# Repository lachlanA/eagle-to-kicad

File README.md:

### **Converting from Eagle to KiCad.**
*    [Quick Introduction Video (DEAD LINK, MOVING to NEW SERVER)](http://cosmosc.com/video/testtital.mp4)  
     *Recommended video player [Firefox 87.0+](https://www.mozilla.org/en-US/firefox/desktop/) with [VLC video player plugin](http://www.videolan.org/vlc/)*  

* The following 5 **ulp** (eagle *user script file*) and one **ulp** include file, work together or stand alone to convert **Eagle** *sch/pcb* version 6.xx*(7.xx-8.xx maybe?)* file(s) and any version of Eagle lib(*lbr*) to **KiCad** *sch/pcb* and *lib/mod* files.  

* The Programs will do
    * Eagle multi sheet schematic to KiCad multi sheets.  
	* Global and local net labels for multi sheets. *(This is a real nasty bit of hacking!)*
	* Multi part gates.  
	* Build KiCad PCB modules and sch libs from Eagle sch.  
	* Make project director to store all the converted files.  
	* And basic error checking.  
	* Eagle 6.xx(7.xx-8.xx?) PCB files can be directly import to KiCad.  
	* Eagle *LBR*s (any version of Eagle libs or size ) can be converted to KiCad lib/mod using eagle-lbr2kicad-1.0.ulp see [Eagle Lib conversion]( https://github.com/lachlanA/eagle-to-kicad-libs) for more details.  
	* Converts VIA to Pads, which helps with KiCad's flood fill, when VIAs have no connections.  
	* Documents fills over SMD pads on Eagle Layer 155,156  
	* Documents on layer's 150,152,153,154 of (Eagle) the unconnected VIAs and tracks.  
	* The **[examples](https://github.com/lachlanA/eagle-to-kicad/tree/master/examples)** directory contains a number of converted schematics/boards.  

* By using the following **ulp**s  a consistent link from the schematic to PCB is maintained so forward and backward net-list annotations work under KiCad!  

* **WARNINGS, AND NASTY SURPRISES, PLEASE READ!!!**
* **Only works correctly for version 4.7, or 5.1.(X?) of KiCad, it may not on other version.**
* **In KiCad Eagle PCB import of vias and tracks don't retain their NET information if they are not connected to a pad with a track, whereas they do in Eagle, (KiCad assigns a null net-name on Eagle PCB import in KiCad's Pcbnew).***  
***The result will be KiCad flood fill will not connect to them!!! There is an option to convert and document on layers 150,152,153,154 of (Eagle) the unconnected VIAs and tracks which will make finding and fixing the problem much easier.***
* ***Schematics wire's/nets can terminate in a bus or onto another wire/net/pad and not be connected in Eagle!!
Whereas in KiCad schematic wires to wires and wires to pads which terminates at the same location will be connected!!***  
* ***Eagle oval pad shapes are not supported in KiCad, you will only end up with a round pad!!***  
* ***Eagle PCB design rules are not imported by KiCads Pcbnew.***  

### Installing.
* Download the zip file, and unzip using your favorite zip program to your target directory *OR* if your prefer git:

			git clone https://github.com/lachlanA/eagle-to-kicad.git  

* **WARNING:**  The ULPs file-name will conflict with Eagles ULPs file-names so  
  **DO NOT install them in Eagle's ULP directory**  

* There are 5 **ULPs** and one **ULP** include file have been hack together.  
***run-me-first-from-eagle-sch.ulp*** .....   stage 1: Start here,  script missing number(s) to parts prefixes.  
***fix_via_hack.ulp*** ..............................   stage 2: Converts unconnected VIAs to pads.  
***eagle6xx-sch-to-kicad-sch.ulp*** ....    stage 3: Build sch and project files, etc  
***exp-lbrs.ulp*** .......................................   stage 4: Extract libs from eagle schematic/PCB  
***eagle-lbr2kicad-1.0.ulp***....................  stage 5: Converts Eagle lbr to KiCad lib/mod  
***eagle_to_kicad_include.inc*** ..........  Include file used by the other 4 ULP\s  

### HOW TO RUN THE ULPs 
 
 **WARNING Always backup your Eagle sch/PCB files before running this program!**  
 
1. Start your Eagle program *(Make sure your using  version 6.xx of Eagle)*

2. Open the eagle sch/PCB  file you wish to convert. Make sure the eagle sch and PCB files are both, Correct and pass all ERC/DRC checks in Eagle.  

3. Next Open the top left hand  **File menu** and select  **Run ULP**  

4. A file requester window will open. Use this to find the location of the ***run-me-first-from-eagle-sch.ulp*** ULP you download from this website. We use this script to make sure all part prefixes are ending in a number  IE:   R0,  X1   etc. as KiCad will ask to renumber any prefix which does not end in a number. *(It may do this any way, but don't worry it won't change any prefixes which have already been numbered unless you tell it too!)*  Keeping prefixes consistent from schematic to PCB will allow net-list forward and back annotation to work in KiCad. Select **OK** *(this will run the script)*.  When this completes all references without a number should have a number appended to them. Note: This number will start from the largest reference number on the sch/PCB.

5. Next stage will run automatically, ***fix_via_hack.ulp*** This will check for free unconnected VIAs and convert them to pads,  this is very much a hack, as it changes the Eagle sch/PCB files.  The changed files are saved in ***targetdir/modified_eagle_files/*** There are 2 option's Document the VIAs/pads buy putting a ***>*** and net lable name on the VIA/pad on **layer 51** for Eagle, and **Dwgs.User** for KiCad. Second option is to Not to convert the VIAs to pads.  
The ulp hack adds pad's to the sch file, at **X,Y 0,0** this may conflict with any net/part at this location, so please move the sch/PCB contents so there are no parts/nets at this location before running the script.
You may getting warnings from Eagle about connecting net??? to a power plan net, just click OK, as this is normal for this script.

6. Next stage will run automatically. Set the option/location of the download ULP. And also Make sure you make/select a ***clean target directory*** where all the KiCad files will be put. Select OK, And with luck you should have sch part done. The previous ULP will link automatically to ***exp-lbrs.ulp*** for the  next step: If you have selected extract the KiCad lib's from Eagle sch/PCB *(The default).* This ULP will build Eagle lbr file, *Note: this can be a very slow process,  and will leave the Eagle PCB editor window open when complete*. Just ignore this for the moment. If this complete OK, the previous ULP will link to ***eagle-lbr2kicad-1.0.ulp*** which will convert the Eagle lbr file to a KiCad lib/mod files.  The ***eagle-lbr2kicad-1.0.ulp*** window will open with quite a few options. Just select OK for the moment.  And if *Murphy's Law is sound asleep* we should have the target directory with all the converted files, including KiCad project files. But with one exception, it will be missing KiCad PCB file.

7. For this, we need to Open KiCad's **pcbnew** program directly, at the command prompt ("c:\Program Files\KiCad\bin\pcbnew.exe"). *If you make the mistake of not opening **pcbnew** directly, and instead chose to run it from KiCad's **pcbnew**  menu. You will have no option for importing the Eagle 6 PCB file!*  In Pcbnew click on **File->Import Non-KiCad Board File...**, a window will pop-up. Select the PCB eagle file linked to the eagle sch file we used at the beginning. On the lower right side you will have a drop down menu box option, select **Eagle ver. 6.x XML PCB files (\*.b**, and press OK. After importing the Eagle PCB file, (without errors I hope). Do a **SAVE AS** to **PROJECTNAME.kicad_pcb** to the new target directory *(where you saved the output from to preceding ULP's to).* **PROJECTNAME** being the name you give to your project early on. As a helper a dummy kicad_pcb file with the correct name has been created in the target directory which you can use to do a Save-As to.

8. Next step is to check the KiCad **sch** and KiCad **PCB** are consistent for parts and nets. Start **KiCad**, and open the project in the newly created target directory. Open the sch file. And if it was converted from the single sch file, you should have the **sch** file in the display. Or multi sheet **sch** file you will have a number of small boxes spread across the page. Each one of those boxes being a converted Eagle sub-sheet. Click on the first one and check for errors. All being good, click on Generate Net-list, and click OK. It may ask to Annotate the **schematic**. If so do the Annotation step. And then come back and click on Generate net-list. And Generate it.

9. Next click on **CvPcb**, this assigns the PCB footprints with the sch parts. Most likely you will get the following warning: *Some of the assigned footprints are legacy entries (are missing lib nicknames). Would you like CvPcb to attempt to convert them to the new required FPID format? (If you answer no, then these assignments will be cleared out and you will have to re-assign these footprints yourself.)* Just click the yes button. And a window will open up listing all the parts and footprints which it has assigned. Under FILE menu click Save. And then File Close.

10. Next Clink on **PcbNew** button on the top menu, and the PCB should open up. Now click on the **NetList** and a window should open up, from there click on Read Current Net-list. All going well you should not have any extra parts added, and only a few warning's about changing net list names.  And you should be done. Please check over the converted **sch/PCB** as there are many things which can go wrong! While I have tried to catch as many conversion problem, I expect there many still waiting to be found. ***So check and triple check the results!!!***

**NOTES:**   For more info on KiCad https://www.kicad.org/display/KICAD/Installing+KiCad  
As KiCad is the process of major upgrade, and enhancement. Please be nice when asking questions of the Development team. I think you will love the new Push and shove router. This feature alone makes it worth while moving from Eagle to KiCad. I hope these ULPs make the job a lot easier.

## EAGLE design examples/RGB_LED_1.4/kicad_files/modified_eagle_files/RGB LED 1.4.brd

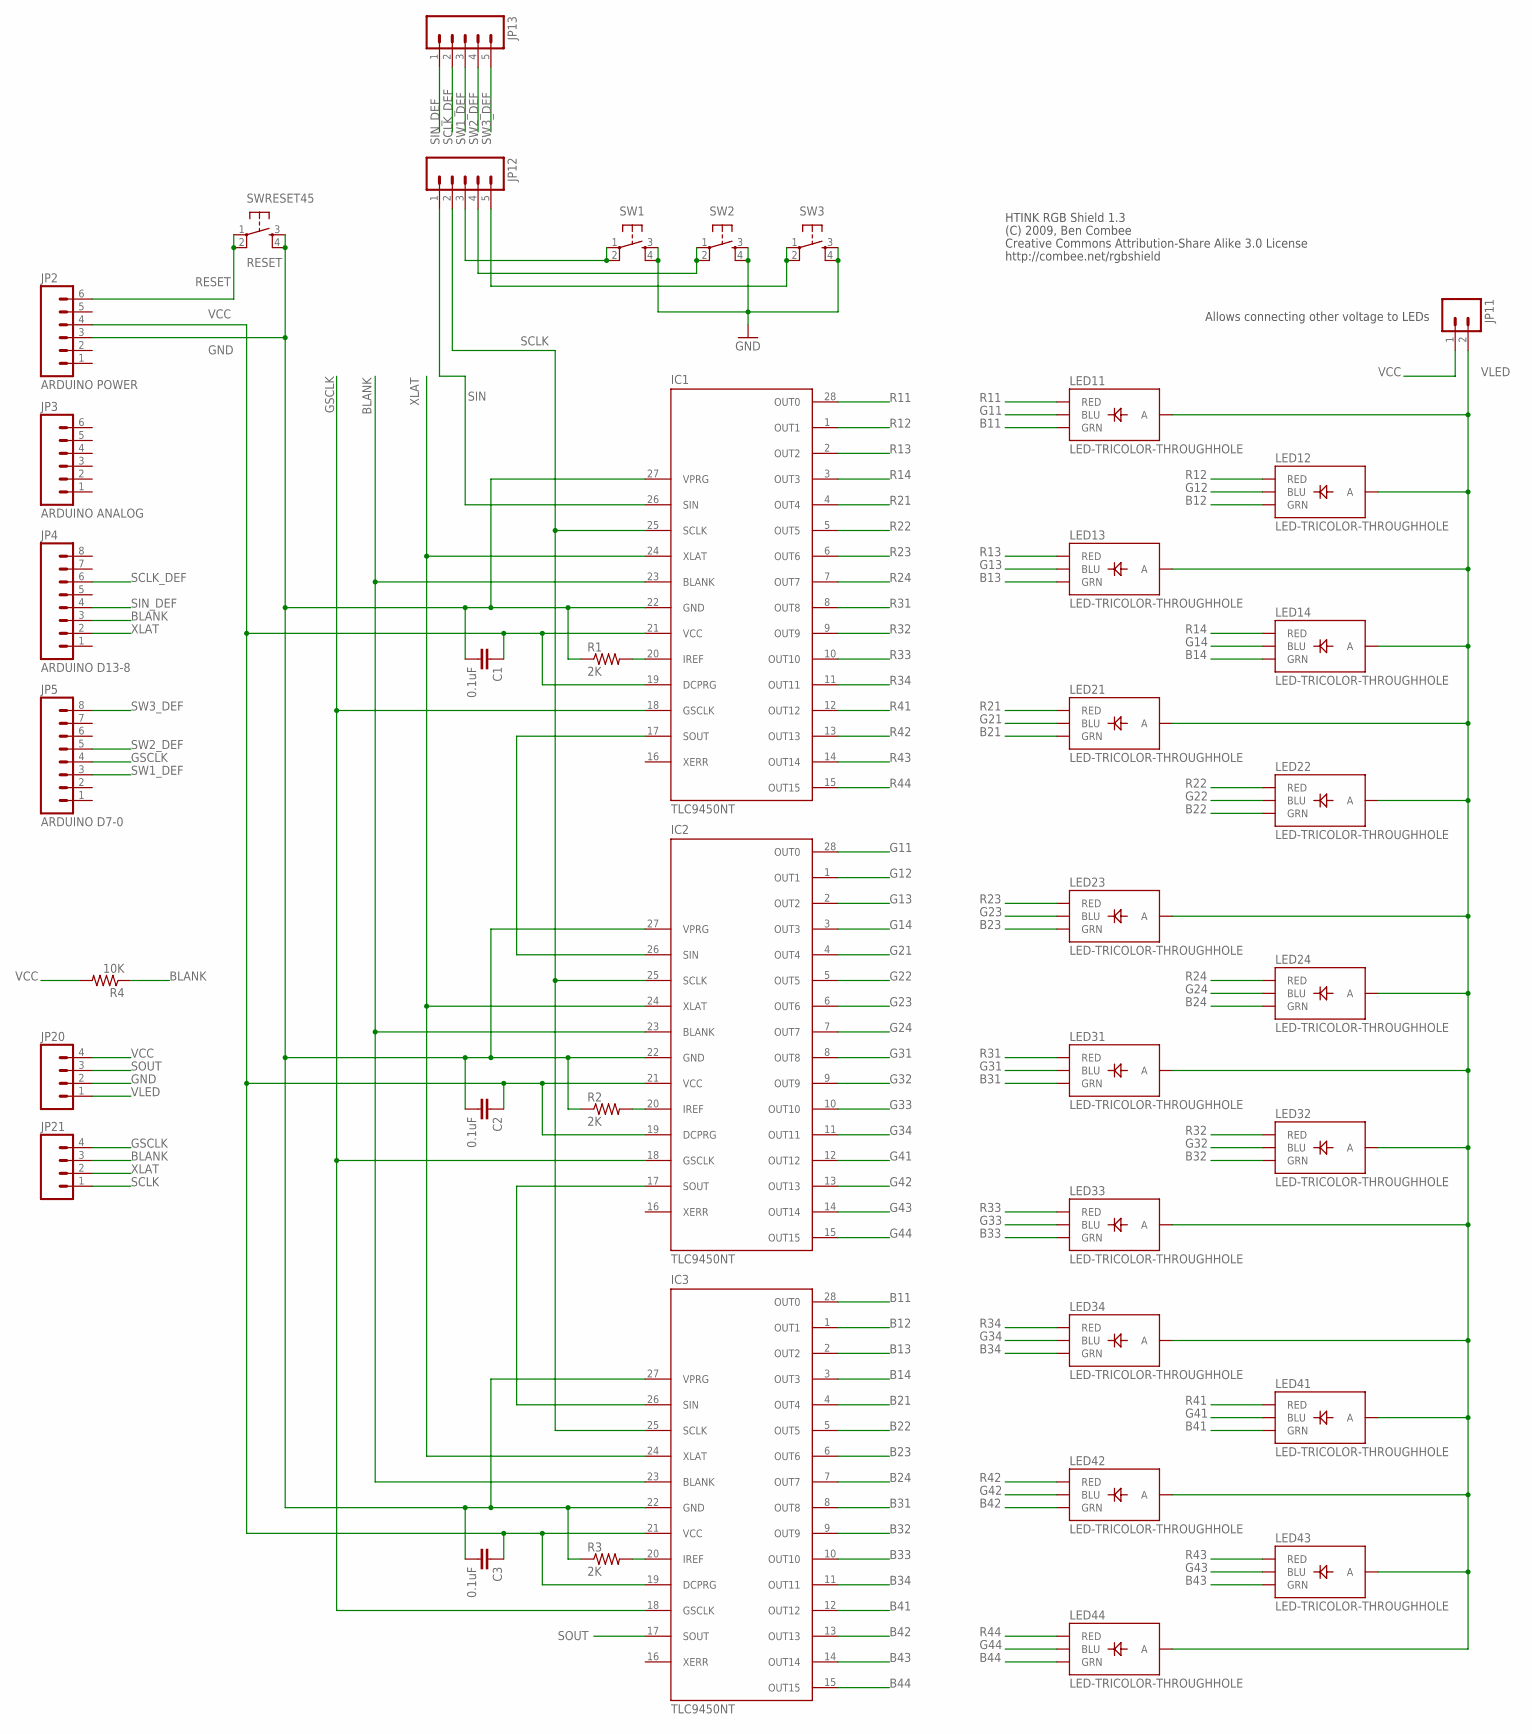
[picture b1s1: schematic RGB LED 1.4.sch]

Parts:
C1, C2, C3: 0.1uF; CAP-PTH-SMALL
IC1, IC2, IC3: TLC9450NT; DIL28-3
JP2: ARDUINO POWER; 1X06_LOCK
JP3: ARDUINO ANALOG; 1X06_LOCK
JP4: ARDUINO D13-8; 1X08_LOCK
JP5: ARDUINO D7-0; 1X08_LOCK
JP11: M02LOCK; 1X02_LOCK
JP12, JP13: M05LOCK; 1X05_LOCK
JP20, JP21: M04LOCK; 1X04_LOCK
LED11, LED12, LED13, LED14, LED21, LED22, LED23, LED24, LED31, LED32, LED33, LED34, LED41, LED42, LED43, LED44: LED-TRICOLOR-THROUGHHOLE
R1, R2, R3: 2K; 0309/12
R4: 10K; 0309/12
SW1, SW2, SW3: TAC_SWITCHPTH; TACTILE-PTH
SWRESET45: RESET; TACTILE-PTH

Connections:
B11: IC3.28 (OUT0), LED11.GRN
B12: IC3.1 (OUT1), LED12.GRN
B13: IC3.2 (OUT2), LED13.GRN
B14: IC3.3 (OUT3), LED14.GRN
B21: IC3.4 (OUT4), LED21.GRN
B22: IC3.5 (OUT5), LED22.GRN
B23: IC3.6 (OUT6), LED23.GRN
B24: IC3.7 (OUT7), LED24.GRN
B31: IC3.8 (OUT8), LED31.GRN
B32: IC3.9 (OUT9), LED32.GRN
B33: IC3.10 (OUT10), LED33.GRN
B34: IC3.11 (OUT11), LED34.GRN
B41: IC3.12 (OUT12), LED41.GRN
B42: IC3.13 (OUT13), LED42.GRN
B43: IC3.14 (OUT14), LED43.GRN
B44: IC3.15 (OUT15), LED44.GRN
BLANK: IC1.23 (BLANK), IC2.23 (BLANK), IC3.23 (BLANK), JP4.3, JP21.3, R4.1
G11: IC2.28 (OUT0), LED11.BLU
G12: IC2.1 (OUT1), LED12.BLU
G13: IC2.2 (OUT2), LED13.BLU
G14: IC2.3 (OUT3), LED14.BLU
G21: IC2.4 (OUT4), LED21.BLU
G22: IC2.5 (OUT5), LED22.BLU
G23: IC2.6 (OUT6), LED23.BLU
G24: IC2.7 (OUT7), LED24.BLU
G31: IC2.8 (OUT8), LED31.BLU
G32: IC2.9 (OUT9), LED32.BLU
G33: IC2.10 (OUT10), LED33.BLU
G34: IC2.11 (OUT11), LED34.BLU
G41: IC2.12 (OUT12), LED41.BLU
G42: IC2.13 (OUT13), LED42.BLU
G43: IC2.14 (OUT14), LED43.BLU
G44: IC2.15 (OUT15), LED44.BLU
GND: C1.2, C2.2, C3.2, IC1.22 (GND), IC1.27 (VPRG), IC2.22 (GND), IC2.27 (VPRG), IC3.22 (GND), IC3.27 (VPRG), JP2.3, JP20.2, R1.1, R2.1, R3.1, SW1.3, SW1.4, SW2.3, SW2.4, SW3.3, SW3.4, SWRESET45.3, SWRESET45.4
GSCLK: IC1.18 (GSCLK), IC2.18 (GSCLK), IC3.18 (GSCLK), JP5.4, JP21.4
unnamed: IC1.17 (SOUT), IC2.26 (SIN)
unnamed: IC2.17 (SOUT), IC3.26 (SIN)
unnamed: JP12.3, SW1.1, SW1.2
unnamed: IC3.20 (IREF), R3.2
unnamed: IC2.20 (IREF), R2.2
unnamed: IC1.20 (IREF), R1.2
unnamed: JP12.4, SW2.1, SW2.2
unnamed: JP12.5, SW3.1, SW3.2
R11: IC1.28 (OUT0), LED11.RED
R12: IC1.1 (OUT1), LED12.RED
R13: IC1.2 (OUT2), LED13.RED
R14: IC1.3 (OUT3), LED14.RED
R21: IC1.4 (OUT4), LED21.RED
R22: IC1.5 (OUT5), LED22.RED
R23: IC1.6 (OUT6), LED23.RED
R24: IC1.7 (OUT7), LED24.RED
R31: IC1.8 (OUT8), LED31.RED
R32: IC1.9 (OUT9), LED32.RED
R33: IC1.10 (OUT10), LED33.RED
R34: IC1.11 (OUT11), LED34.RED
R41: IC1.12 (OUT12), LED41.RED
R42: IC1.13 (OUT13), LED42.RED
R43: IC1.14 (OUT14), LED43.RED
R44: IC1.15 (OUT15), LED44.RED
RESET: JP2.6, SWRESET45.1, SWRESET45.2
SCLK: IC1.25 (SCLK), IC2.25 (SCLK), IC3.25 (SCLK), JP12.2, JP21.1
SCLK_DEF: JP4.6, JP13.2
SIN: IC1.26 (SIN), JP12.1
SIN_DEF: JP4.4, JP13.1
SOUT: IC3.17 (SOUT), JP20.3
SW1_DEF: JP5.3, JP13.3
SW2_DEF: JP5.5, JP13.4
SW3_DEF: JP5.8, JP13.5
VCC: C1.1, C2.1, C3.1, IC1.19 (DCPRG), IC1.21 (VCC), IC2.19 (DCPRG), IC2.21 (VCC), IC3.19 (DCPRG), IC3.21 (VCC), JP2.4, JP11.1, JP20.4, R4.2
VLED: JP11.2, JP20.1, LED11.GND (A), LED12.GND (A), LED13.GND (A), LED14.GND (A), LED21.GND (A), LED22.GND (A), LED23.GND (A), LED24.GND (A), LED31.GND (A), LED32.GND (A), LED33.GND (A), LED34.GND (A), LED41.GND (A), LED42.GND (A), LED43.GND (A), LED44.GND (A)
XLAT: IC1.24 (XLAT), IC2.24 (XLAT), IC3.24 (XLAT), JP4.2, JP21.2

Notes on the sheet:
HTINK RGB Shield 1.3
(C) 2009, Ben Combee
Creative Commons Attribution-Share Alike 3.0 License
http://combee.net/rgbshield
Allows connecting other voltage to LEDs

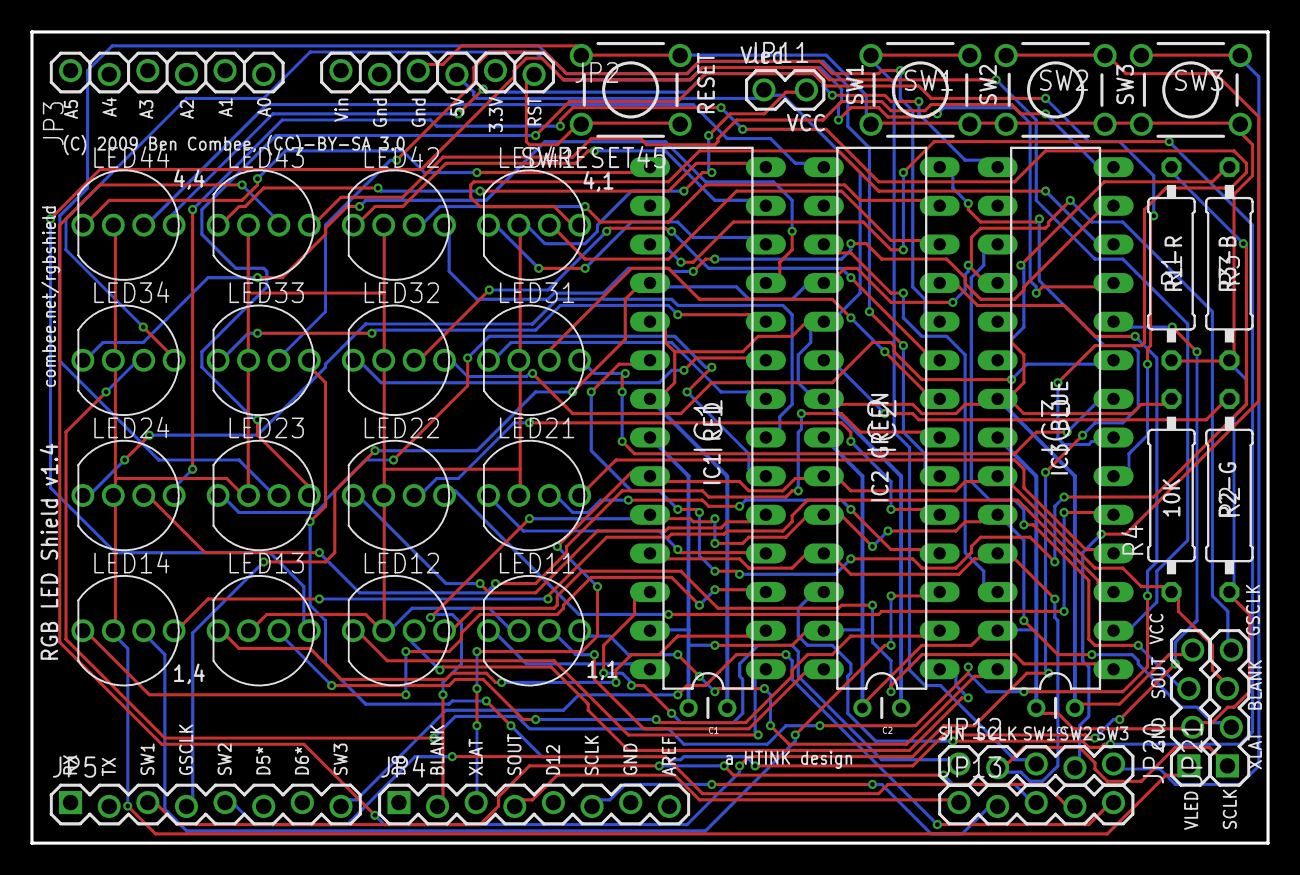
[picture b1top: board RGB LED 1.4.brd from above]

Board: 2 copper layers, 81.3 x 53.3 mm, 39 parts (0 on the bottom side), 71 nets.

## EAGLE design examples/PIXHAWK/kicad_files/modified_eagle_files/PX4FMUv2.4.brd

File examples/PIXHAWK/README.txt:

NOTE: ***** USE AT YOUR OWN RISK *****

This contains the eagle file's from PX4 Autopilot Project from git-hub, at https://github.com/PX4 which have been
convert to KiCad. Via's have been converted to Pad, and the modified Eagle files are in

  kicad_files/modified_eagle_files/

The original Eagle files are in

  eagle_original_files/

Also note the Eagle files have been converted to version 6.xx of eagle.
Note:  No Adjustment of power plan's had been made, you will need to adjust them to get correct connection's
       and spacing etc. And as away triple check you results.

sources at:   https://github.com/PX4

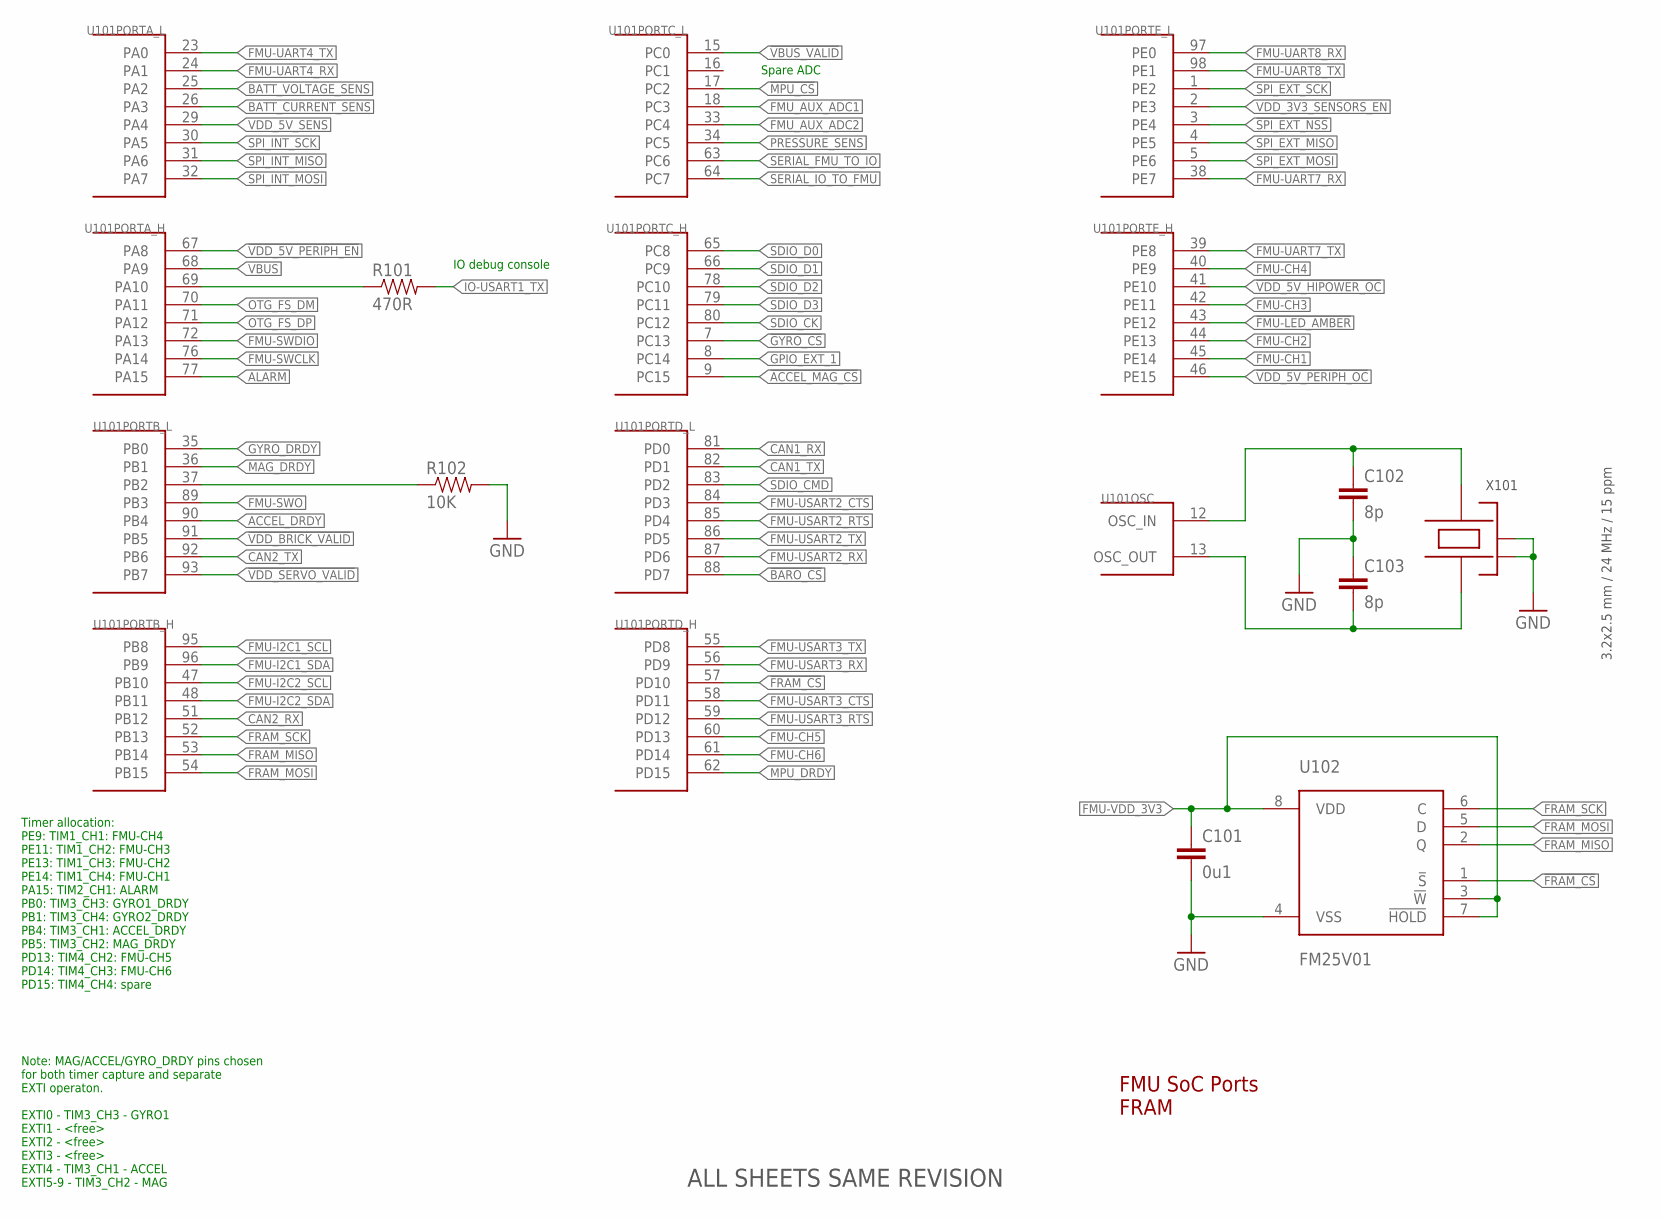
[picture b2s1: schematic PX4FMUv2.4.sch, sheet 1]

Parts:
C101: 0u1; 0402-CAP; PARTNO CC0402ZRY5V7BB104
C102, C103: 8p; 0402-CAP; PARTNO C1005C0G1H080C
R101: 470R; 0402-RES; PARTNO RC0402FR-07470RL
R102: 10K; 0402-RES; PARTNO RC0402FR-0710KL
U101: STM32F4X7VX; TQFP100; PARTNO STM32F427VI
U102: FM25V01; SO08; PARTNO FM25V01-G
X101: 3.2x2.5 mm / 24 MHz / 15 ppm; OSCILLATOR-3.2X2.5; PARTNO NX3225SA-24.000000MHZ

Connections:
!ACCEL_MAG_CS: U101.9 (PC15); also elsewhere on the board
!BARO_CS: U101.88 (PD7); also elsewhere on the board
!FMU-LED_AMBER: U101.43 (PE12); also elsewhere on the board
!FRAM_CS: U101.57 (PD10), U102.1 (!S)
!GYRO_CS: U101.7 (PC13); also elsewhere on the board
!MPU_CS: U101.17 (PC2); also elsewhere on the board
!SPI_EXT_NSS: U101.3 (PE4); also elsewhere on the board
!VBUS_VALID: U101.15 (PC0); also elsewhere on the board
!VDD_5V_HIPOWER_OC: U101.41 (PE10); also elsewhere on the board
!VDD_5V_PERIPH_EN: U101.67 (PA8); also elsewhere on the board
!VDD_5V_PERIPH_OC: U101.46 (PE15); also elsewhere on the board
!VDD_BRICK_VALID: U101.91 (PB5); also elsewhere on the board
!VDD_SERVO_VALID: U101.93 (PB7); also elsewhere on the board
ACCEL_DRDY: U101.90 (PB4); also elsewhere on the board
ALARM: U101.77 (PA15); also elsewhere on the board
BATT_CURRENT_SENS: U101.26 (PA3); also elsewhere on the board
BATT_VOLTAGE_SENS: U101.25 (PA2); also elsewhere on the board
CAN1_RX: U101.81 (PD0); also elsewhere on the board
CAN1_TX: U101.82 (PD1); also elsewhere on the board
CAN2_RX: U101.51 (PB12); also elsewhere on the board
CAN2_TX: U101.92 (PB6); also elsewhere on the board
FMU-CH1: U101.45 (PE14); also elsewhere on the board
FMU-CH2: U101.44 (PE13); also elsewhere on the board
FMU-CH3: U101.42 (PE11); also elsewhere on the board
FMU-CH4: U101.40 (PE9); also elsewhere on the board
FMU-CH5: U101.60 (PD13); also elsewhere on the board
FMU-CH6: U101.61 (PD14); also elsewhere on the board
FMU-I2C1_SCL: U101.95 (PB8); also elsewhere on the board
FMU-I2C1_SDA: U101.96 (PB9); also elsewhere on the board
FMU-I2C2_SCL: U101.47 (PB10); also elsewhere on the board
FMU-I2C2_SDA: U101.48 (PB11); also elsewhere on the board
FMU-SWCLK: U101.76 (PA14); also elsewhere on the board
FMU-SWDIO: U101.72 (PA13); also elsewhere on the board
FMU-SWO: U101.89 (PB3); also elsewhere on the board
FMU-UART4_RX: U101.24 (PA1); also elsewhere on the board
FMU-UART4_TX: U101.23 (PA0); also elsewhere on the board
FMU-UART7_RX: U101.38 (PE7); also elsewhere on the board
FMU-UART7_TX: U101.39 (PE8); also elsewhere on the board
FMU-UART8_RX: U101.97 (PE0); also elsewhere on the board
FMU-UART8_TX: U101.98 (PE1); also elsewhere on the board
FMU-USART2_CTS: U101.84 (PD3); also elsewhere on the board
FMU-USART2_RTS: U101.85 (PD4); also elsewhere on the board
FMU-USART2_RX: U101.87 (PD6); also elsewhere on the board
FMU-USART2_TX: U101.86 (PD5); also elsewhere on the board
FMU-USART3_CTS: U101.58 (PD11); also elsewhere on the board
FMU-USART3_RTS: U101.59 (PD12); also elsewhere on the board
FMU-USART3_RX: U101.56 (PD9); also elsewhere on the board
FMU-USART3_TX: U101.55 (PD8); also elsewhere on the board
FMU-VDD_3V3: C101.P$1 (1), U102.3 (!W), U102.7 (!HOLD), U102.8 (VDD); also elsewhere on the board
FMU_AUX_ADC1: U101.18 (PC3); also elsewhere on the board
FMU_AUX_ADC2: U101.33 (PC4); also elsewhere on the board
FRAM_MISO: U101.53 (PB14), U102.2 (Q)
FRAM_MOSI: U101.54 (PB15), U102.5 (D)
FRAM_SCK: U101.52 (PB13), U102.6 (C)
GND: C101.P$2 (2), C102.P$2 (2), C103.P$1 (1), R102.P$2 (2), U102.4 (VSS), X101.2 (NC_2), X101.4 (NC_4); also elsewhere on the board
GPIO_EXT_1: U101.8 (PC14); also elsewhere on the board
GYRO_DRDY: U101.35 (PB0); also elsewhere on the board
IO-USART1_TX: R101.P$2 (2); also elsewhere on the board
MAG_DRDY: U101.36 (PB1); also elsewhere on the board
MPU_DRDY: U101.62 (PD15); also elsewhere on the board
unnamed: C103.P$2 (2), U101.13 (OSC_OUT), X101.1
unnamed: C102.P$1 (1), U101.12 (OSC_IN), X101.3
unnamed: R101.P$1 (1), U101.69 (PA10)
OTG_FS_DM: U101.70 (PA11); also elsewhere on the board
OTG_FS_DP: U101.71 (PA12); also elsewhere on the board
PB2-BOOT1: R102.P$1 (1), U101.37 (PB2)
PRESSURE_SENS: U101.34 (PC5); also elsewhere on the board
SDIO_CK: U101.80 (PC12); also elsewhere on the board
SDIO_CMD: U101.83 (PD2); also elsewhere on the board
SDIO_D0: U101.65 (PC8); also elsewhere on the board
SDIO_D1: U101.66 (PC9); also elsewhere on the board
SDIO_D2: U101.78 (PC10); also elsewhere on the board
SDIO_D3: U101.79 (PC11); also elsewhere on the board
SERIAL_FMU_TO_IO: U101.63 (PC6); also elsewhere on the board
SERIAL_IO_TO_FMU: U101.64 (PC7); also elsewhere on the board
SPI_EXT_MISO: U101.4 (PE5); also elsewhere on the board
SPI_EXT_MOSI: U101.5 (PE6); also elsewhere on the board
SPI_EXT_SCK: U101.1 (PE2); also elsewhere on the board
SPI_INT_MISO: U101.31 (PA6); also elsewhere on the board
SPI_INT_MOSI: U101.32 (PA7); also elsewhere on the board
SPI_INT_SCK: U101.30 (PA5); also elsewhere on the board
VBUS: U101.68 (PA9); also elsewhere on the board
VDD_3V3_SENSORS_EN: U101.2 (PE3); also elsewhere on the board
VDD_5V_SENS: U101.29 (PA4); also elsewhere on the board

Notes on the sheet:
FMU SoC Ports FRAM
Note: MAG/ACCEL/GYRO_DRDY pins chosen for both timer capture and separate EXTI operaton. EXTI0 - TIM3_CH3 - GYRO1 EXTI1 - <free> EXTI2 - <free> EXTI3 - <free> EXTI4 - TIM3_CH1 - ACCEL EXTI5-9 - TIM3_CH2 - MAG
Timer allocation: PE9: TIM1_CH1: FMU-CH4 PE11: TIM1_CH2: FMU-CH3 PE13: TIM1_CH3: FMU-CH2 PE14: TIM1_CH4: FMU-CH1 PA15: TIM2_CH1: ALARM PB0: TIM3_CH3: GYRO1_DRDY PB1: TIM3_CH4: GYRO2_DRDY PB4: TIM3_CH1: ACCEL_DRDY PB5: TIM3_CH2: MAG_DRDY PD13: TIM4_CH2: FMU-CH5 PD14: TIM4_CH3: FMU-CH6 PD15: TIM4_CH4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
IO debug console
Spare ADC
ALL SHEETS SAME REVISION

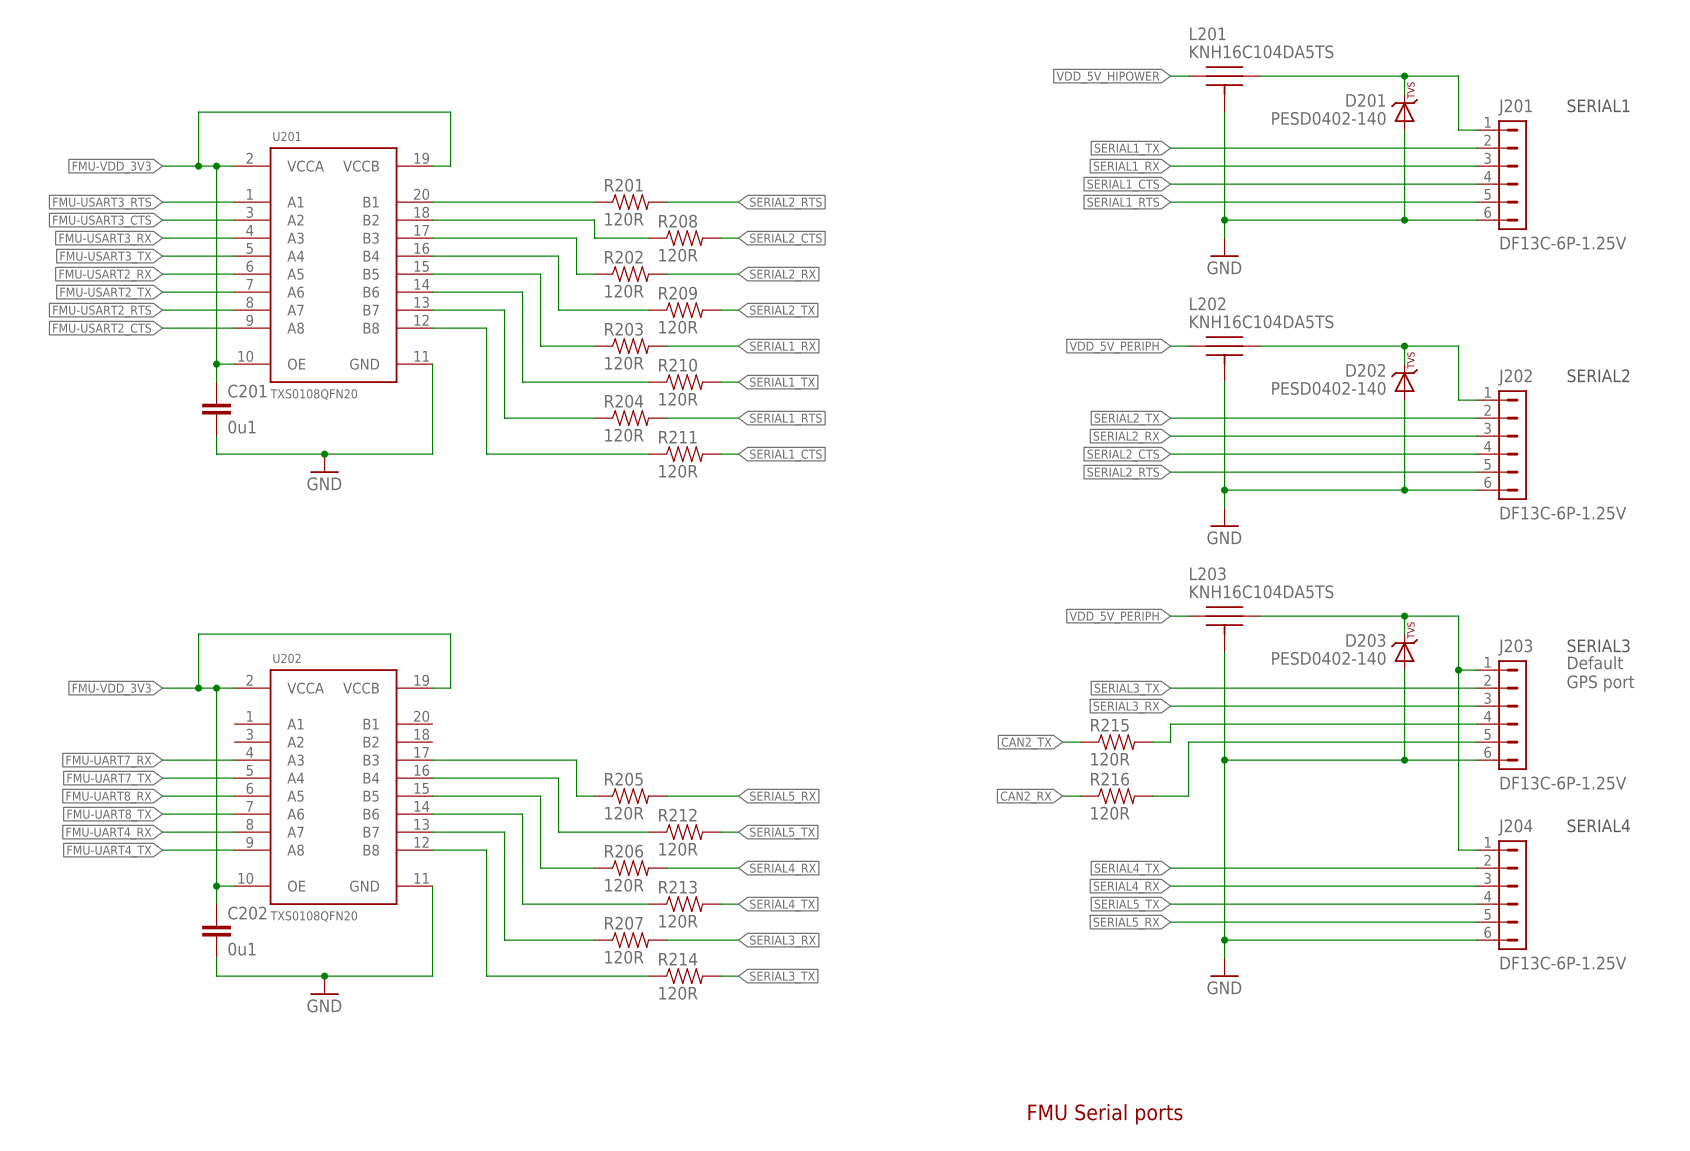
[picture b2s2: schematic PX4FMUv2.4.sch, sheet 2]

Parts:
C201, C202: 0u1; 0402-CAP; PARTNO CC0402ZRY5V7BB104
D201, D202, D203: PESD0402-140; 0402-TVS; PARTNO PESD0402-140
J201, J202, J203, J204: DF13C-6P-1.25V; PARTNO DF13C-6P-1.25V(20)
L201, L202, L203: KNH16C104DA5TS; KYOCERA-KNH16-DA; PARTNO KNH16C104DA5TS
R201, R202, R203, R204, R205, R206, R207, R208, R209, R210, R211, R212, R213, R214, R215, R216: 120R; 0402-RES; PARTNO RC0402FR-07120RL
U201, U202: TXS0108QFN20; QFN20-RGY; PARTNO TXS0108ERGYR

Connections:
CAN2_RX: R216.P$1 (1); also elsewhere on the board
CAN2_TX: R215.P$1 (1); also elsewhere on the board
FMU-UART4_RX: U202.8 (A7); also elsewhere on the board
FMU-UART4_TX: U202.9 (A8); also elsewhere on the board
FMU-UART7_RX: U202.4 (A3); also elsewhere on the board
FMU-UART7_TX: U202.5 (A4); also elsewhere on the board
FMU-UART8_RX: U202.6 (A5); also elsewhere on the board
FMU-UART8_TX: U202.7 (A6); also elsewhere on the board
FMU-USART2_CTS: U201.9 (A8); also elsewhere on the board
FMU-USART2_RTS: U201.8 (A7); also elsewhere on the board
FMU-USART2_RX: U201.6 (A5); also elsewhere on the board
FMU-USART2_TX: U201.7 (A6); also elsewhere on the board
FMU-USART3_CTS: U201.3 (A2); also elsewhere on the board
FMU-USART3_RTS: U201.1 (A1); also elsewhere on the board
FMU-USART3_RX: U201.4 (A3); also elsewhere on the board
FMU-USART3_TX: U201.5 (A4); also elsewhere on the board
FMU-VDD_3V3: C201.P$1 (1), C202.P$1 (1), U201.2 (VCCA), U201.10 (OE), U201.19 (VCCB), U202.2 (VCCA), U202.10 (OE), U202.19 (VCCB); also elsewhere on the board
GND: C201.P$2 (2), C202.P$2 (2), D201.A, D202.A, D203.A, J201.6, J202.6, J203.6, J204.6, L201.P$3, L201.P$4, L201.P$5, L202.P$3, L202.P$4, L202.P$5, L203.P$3, L203.P$4, L203.P$5, U201.11 (GND), U202.11 (GND); also elsewhere on the board
unnamed: D201.C, J201.1, L201.P$2
unnamed: J203.4, R215.P$2 (2)
unnamed: J203.5, R216.P$2 (2)
unnamed: R201.P$1 (1), U201.20 (B1)
unnamed: R208.P$1 (1), U201.18 (B2)
unnamed: R202.P$1 (1), U201.17 (B3)
unnamed: R209.P$1 (1), U201.16 (B4)
unnamed: R203.P$1 (1), U201.15 (B5)
unnamed: R210.P$1 (1), U201.14 (B6)
unnamed: R204.P$1 (1), U201.13 (B7)
unnamed: R211.P$1 (1), U201.12 (B8)
unnamed: R207.P$1 (1), U202.13 (B7)
unnamed: R214.P$1 (1), U202.12 (B8)
unnamed: R205.P$1 (1), U202.17 (B3)
unnamed: R212.P$1 (1), U202.16 (B4)
unnamed: R206.P$1 (1), U202.15 (B5)
unnamed: R213.P$1 (1), U202.14 (B6)
unnamed: D203.C, J203.1, J204.1, L203.P$2
unnamed: D202.C, J202.1, L202.P$2
SERIAL1_CTS: J201.4, R211.P$2 (2)
SERIAL1_RTS: J201.5, R204.P$2 (2)
SERIAL1_RX: J201.3, R203.P$2 (2); also elsewhere on the board
SERIAL1_TX: J201.2, R210.P$2 (2); also elsewhere on the board
SERIAL2_CTS: J202.4, R208.P$2 (2)
SERIAL2_RTS: J202.5, R201.P$2 (2)
SERIAL2_RX: J202.3, R202.P$2 (2); also elsewhere on the board
SERIAL2_TX: J202.2, R209.P$2 (2); also elsewhere on the board
SERIAL3_RX: J203.3, R207.P$2 (2); also elsewhere on the board
SERIAL3_TX: J203.2, R214.P$2 (2); also elsewhere on the board
SERIAL4_RX: J204.3, R206.P$2 (2); also elsewhere on the board
SERIAL4_TX: J204.2, R213.P$2 (2); also elsewhere on the board
SERIAL5_RX: J204.5, R205.P$2 (2); also elsewhere on the board
SERIAL5_TX: J204.4, R212.P$2 (2); also elsewhere on the board
VDD_5V_HIPOWER: L201.P$1; also elsewhere on the board
VDD_5V_PERIPH: L202.P$1, L203.P$1; also elsewhere on the board

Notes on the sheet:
FMU Serial ports
SERIAL2
SERIAL1
SERIAL3
SERIAL4
Default GPS port

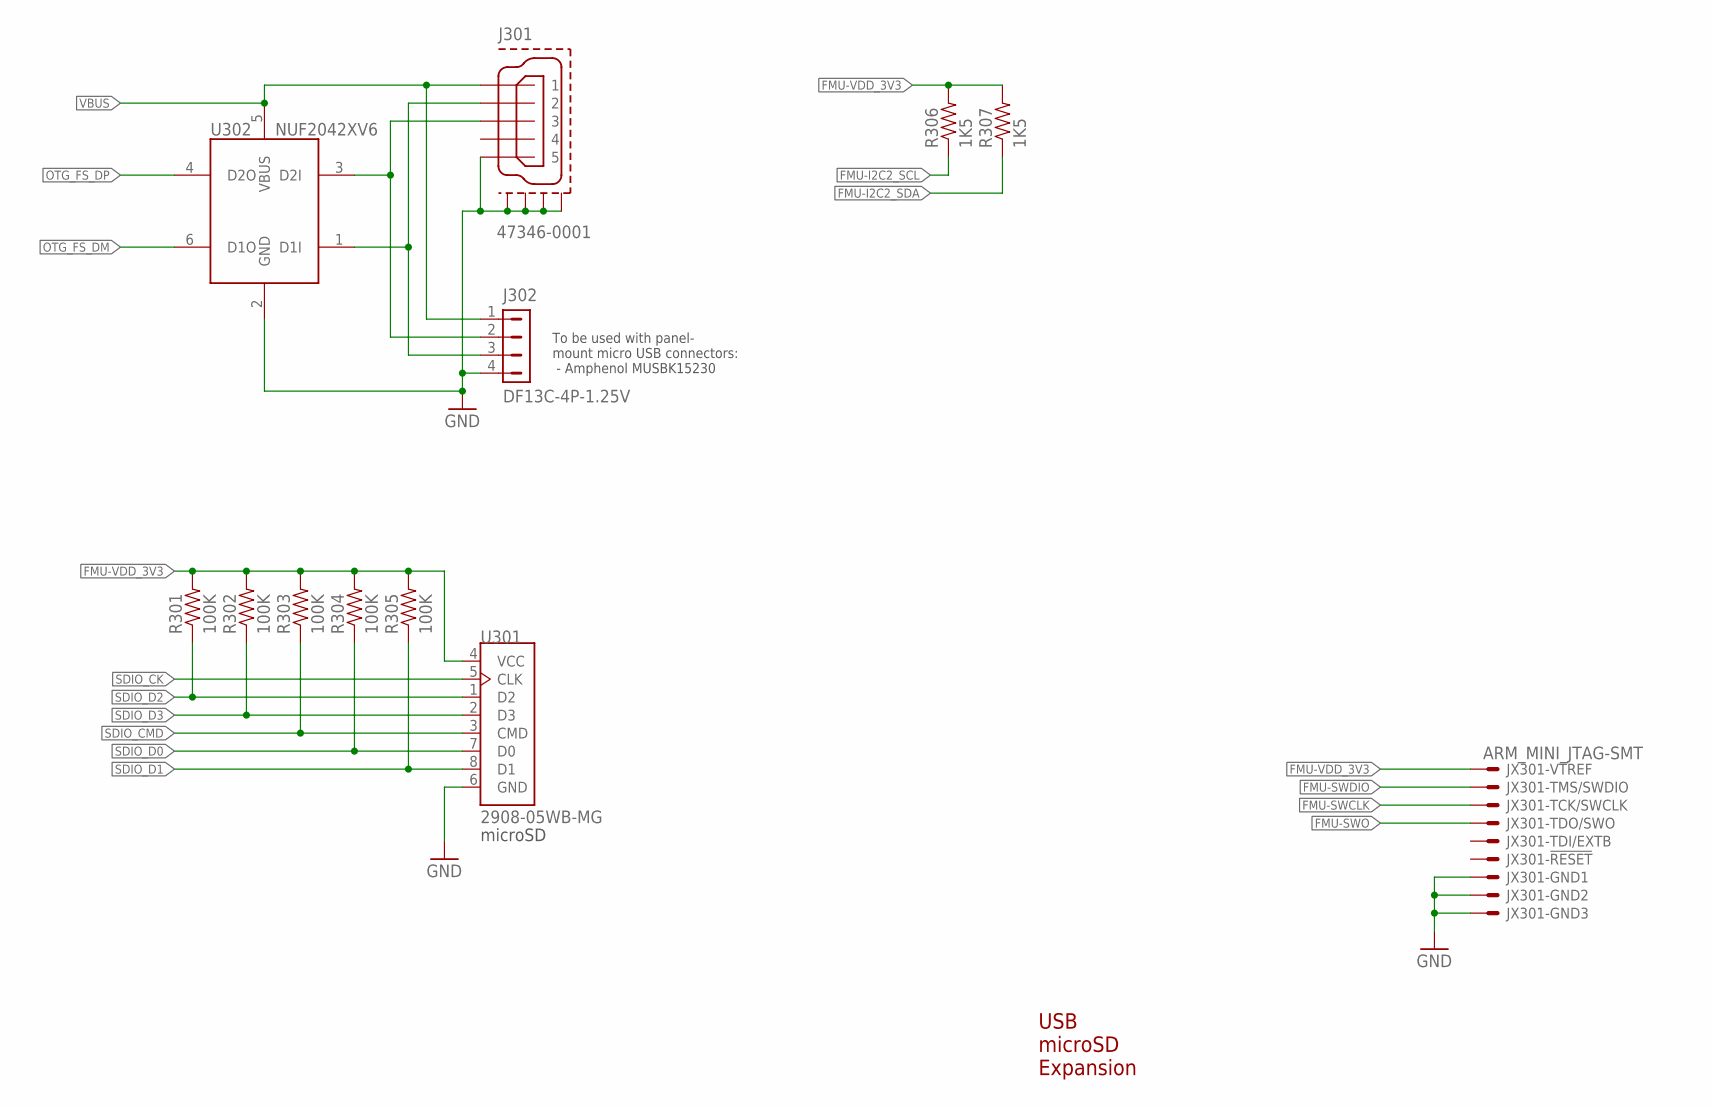
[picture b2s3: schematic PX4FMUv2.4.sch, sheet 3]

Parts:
J301: 47346-0001; MOLEX-47346-0001; PARTNO 47346-0001
J302: DF13C-4P-1.25V; PARTNO DF13C-4P-1.25V(20)
JX301: ARM_MINI_JTAG-SMT; FTSH-105-01-XXX-DV-K; PARTNO M50-3900542
R301, R302, R303, R304, R305: 100K; 0402-RES; PARTNO RC0402FR-07100KL
R306, R307: 1K5; 0402-RES; PARTNO RC0402FR-071K5L
U301: 2908-05WB-MG; MICROSD; PARTNO 2908-05WB-MG
U302: NUF2042XV6; SOT563-6; PARTNO NUF2042XV6T1G

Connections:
FMU-I2C2_SCL: R306.P$1 (1); also elsewhere on the board
FMU-I2C2_SDA: R307.P$1 (1); also elsewhere on the board
FMU-SWCLK: JX301.4; also elsewhere on the board
FMU-SWDIO: JX301.2; also elsewhere on the board
FMU-SWO: JX301.6; also elsewhere on the board
FMU-VDD_3V3: JX301.1, R301.P$2 (2), R302.P$2 (2), R303.P$2 (2), R304.P$2 (2), R305.P$2 (2), R306.P$2 (2), R307.P$2 (2), U301.4 (VCC); also elsewhere on the board
GND: J301.GND (5), J301.GND1, J301.GND2, J301.GND3, J301.GND4, J302.4, JX301.3, JX301.5, JX301.9, U301.6 (GND), U302.2 (GND); also elsewhere on the board
OTG_DM1: J301.D- (2), J302.3, U302.1 (D1I)
OTG_DP1: J301.D+ (3), J302.2, U302.3 (D2I)
OTG_FS_DM: U302.6 (D1O); also elsewhere on the board
OTG_FS_DP: U302.4 (D2O); also elsewhere on the board
SDIO_CK: U301.5 (CLK); also elsewhere on the board
SDIO_CMD: R303.P$1 (1), U301.3 (CMD); also elsewhere on the board
SDIO_D0: R304.P$1 (1), U301.7 (D0); also elsewhere on the board
SDIO_D1: R305.P$1 (1), U301.8 (D1); also elsewhere on the board
SDIO_D2: R301.P$1 (1), U301.1 (D2); also elsewhere on the board
SDIO_D3: R302.P$1 (1), U301.2 (D3); also elsewhere on the board
VBUS: J301.VBUS (1), J302.1, U302.5 (VBUS); also elsewhere on the board

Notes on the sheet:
USB microSD Expansion
microSD
To be used with panel- mount micro USB connectors: - Amphenol MUSBK15230

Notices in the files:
examples/OLINUXINO/RT5350F-OLinuXino-B/eagle_files/RT5350F_OLinuXino_Rev_B.brd:
(C) 2014
examples/PIXHAWK/kicad_files/modified_eagle_files/PX4FMUv2.4.brd:
(c) 2013 mjs/lm/jo
examples/RGB_LED_1.4/kicad_files/modified_eagle_files/RGB LED 1.4.brd:
(C) 2009 Ben Combee, (CC)-BY-SA 3.0
